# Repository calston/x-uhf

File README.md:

# X-UHF

The X-UHF is a modular RF prototyping system for amateur use.

This repo contains STL files and Kicad PCB designs and schematics for different modules.

## Testing

This table reflects modules which have actually been built and performance tested.

|Module      | PCB tested | Frequency tested | Design tested | 
|------------|------------|------------------|---------------|
|SA612 Module| Yes        | 50 Mhz           | Yes           |
|SI5351      | NO         | N/A              | NO            |
|SI5351-BX   | YES        | 100 Mhz          | Yes           |
|DRA818      | NO         | N/A              | NO            |

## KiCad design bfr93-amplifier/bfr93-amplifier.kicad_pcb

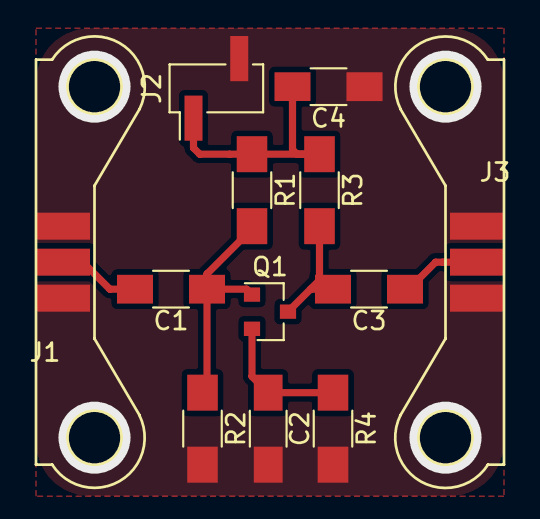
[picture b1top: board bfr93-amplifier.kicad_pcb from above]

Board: 2 copper layers, 12 parts (0 on the bottom side), 7 nets.

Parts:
C1, C2, C3: 100n; C_1206_HandSoldering
C4: 10u; C_1206_HandSoldering
J1: IN; X-UHF_Interconnect
J2: PWR; Pin_Header_Straight_1x02_Pitch2.54mm_SMD_Pin1Left
J3: OUT; X-UHF_Interconnect
Q1: BFR93A; SOT-23
R1, R2: 1K; R_1206_HandSoldering
R3, R4: 220; R_1206_HandSoldering

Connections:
Earth: C2.2, C4.1, J1.1, J1.3, J2.2, J3.1, J3.3, R2.2, R4.2
unnamed: C1.1, Q1.1, R1.2, R2.1
unnamed: C1.2, J1.2
unnamed: C2.1, Q1.2, R4.1
unnamed: C3.1, J3.2
unnamed: C3.2, Q1.3, R3.2
VCC: C4.2, J2.1, R1.1, R3.1

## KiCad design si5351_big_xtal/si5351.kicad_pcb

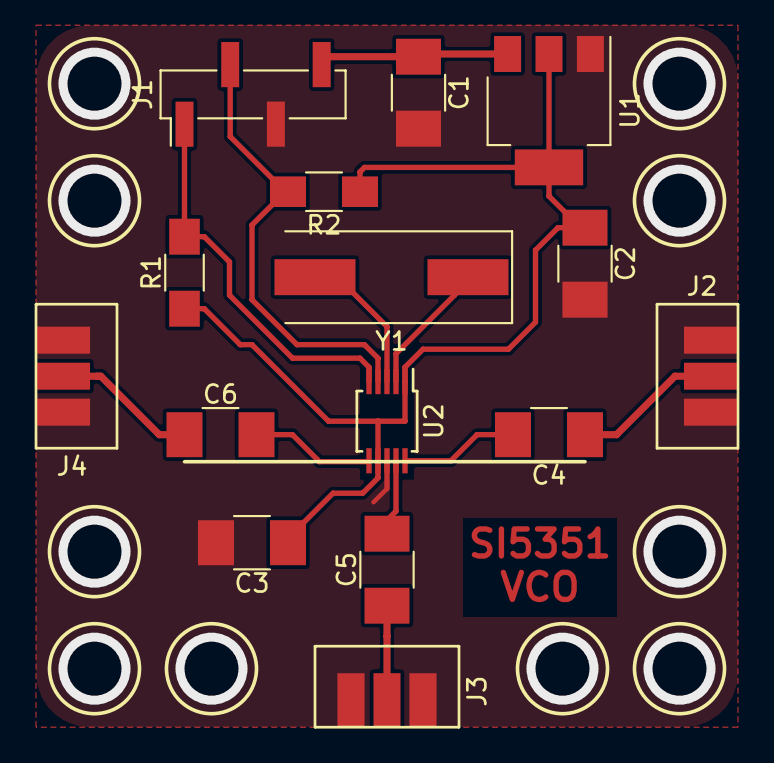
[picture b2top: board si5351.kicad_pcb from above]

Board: 2 copper layers, 15 parts (0 on the bottom side), 13 nets.

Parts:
C1: 10u; C_1210_HandSoldering
C2, C3: 1u; C_1210_HandSoldering
C4, C5, C6: 100n; C_1210_HandSoldering
J1: PWR_IIC; Pin_Header_Straight_1x04_Pitch2.54mm_SMD_Pin1Left
J2: CLK0; X-UHF_Interconnect
J3: CLK1; X-UHF_Interconnect
J4: CLK2; X-UHF_Interconnect
R1, R2: 10k; R_1206_HandSoldering
U1: LD1117-3.3; SOT-223-3_TabPin2
U2: SI5351A; MSOP-10_3x3mm_Pitch0.5mm
Y1: Crystal; Crystal_SMD_HC49-SD

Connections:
Earth: C1.2, C2.2, C3.2, J1.3, J2.1, J2.3, J3.1, J3.3, J4.1, J4.3, U1.1, U2.8
unnamed: C1.1, J1.4, U1.3
unnamed: C2.1, C3.1, R1.1, R2.1, U1.2, U2.1, U2.7
unnamed: C4.1, J2.2
unnamed: C4.2, U2.10
unnamed: C5.1, J3.2
unnamed: C5.2, U2.9
unnamed: C6.1, J4.2
unnamed: C6.2, U2.6
unnamed: J1.1, R1.2, U2.5
unnamed: J1.2, R2.2, U2.4
unnamed: U2.2, Y1.1
unnamed: U2.3, Y1.2

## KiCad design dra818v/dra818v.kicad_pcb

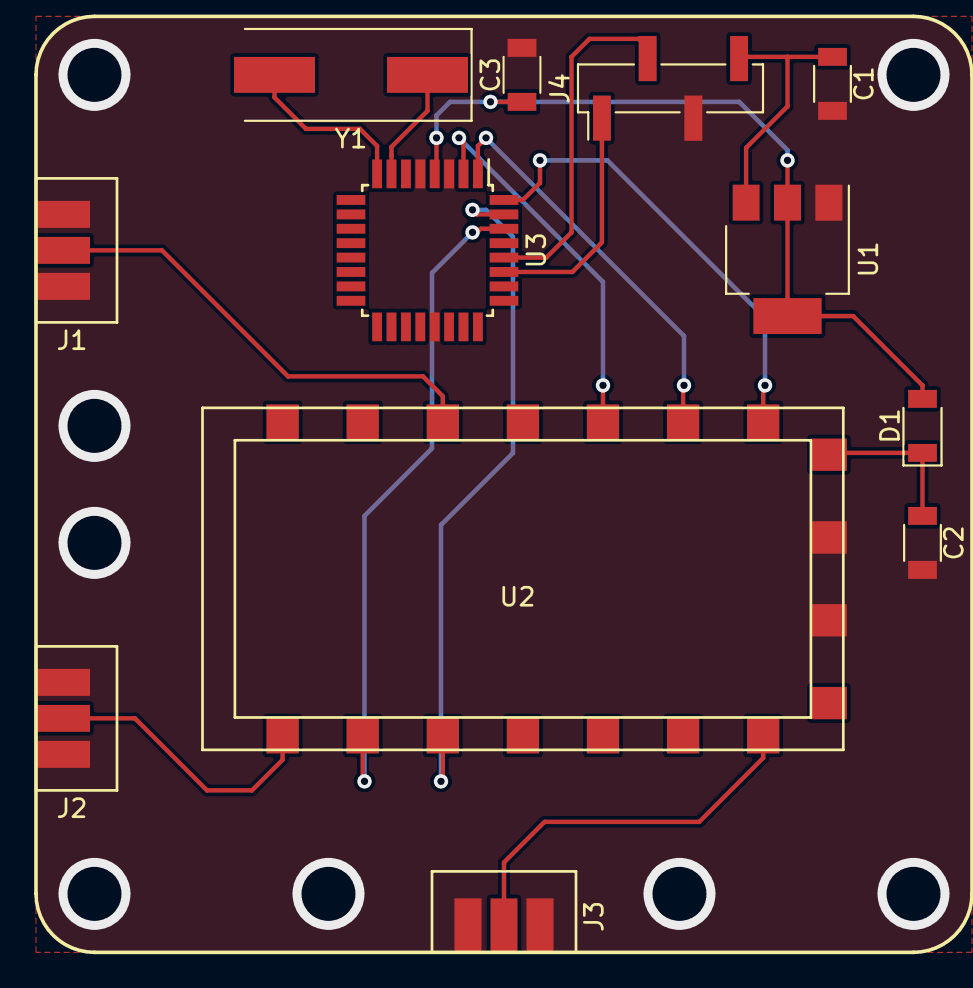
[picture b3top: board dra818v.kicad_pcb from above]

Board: 2 copper layers, 12 parts (0 on the bottom side), 16 nets.

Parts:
C1: 10uF; C_1206
C2, C3: 1uF; C_1206
D1: 1N4001; D_1206
J1: AF_OUT; X-UHF_Interconnect
J2: AF_IN; X-UHF_Interconnect
J3: RF; X-UHF_Interconnect
J4: Conn_01x04; Pin_Header_Straight_1x04_Pitch2.54mm_SMD_Pin1Left
U1: LD1117S50TR_SOT223; SOT-223-3_TabPin2
U2: DRA818V; DRA818
U3: ATmega328P-AU; TQFP-32_7x7mm_Pitch0.8mm
Y1: 16M; Crystal_SMD_HC49-SD

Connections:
Earth: C1.2, C2.2, C3.2, J1.1, J1.3, J2.1, J2.3, J3.1, J3.3, J4.3, U1.1, U2.9, U2.10, U3.3, U3.5, U3.21
unnamed: C1.1, J4.4, U1.3
unnamed: C2.1, D1.1, U2.8
unnamed: C3.1, D1.2, U1.2, U3.4, U3.6, U3.18
unnamed: J1.2, U2.3
unnamed: J2.2, U2.18
unnamed: J3.2, U2.12
unnamed: J4.1, U3.27
unnamed: J4.2, U3.28
unnamed: U2.5, U3.2
unnamed: U2.6, U3.1
unnamed: U2.7, U3.32
unnamed: U2.16, U3.31
unnamed: U2.17, U3.30
unnamed: U3.7, Y1.1
unnamed: U3.8, Y1.2

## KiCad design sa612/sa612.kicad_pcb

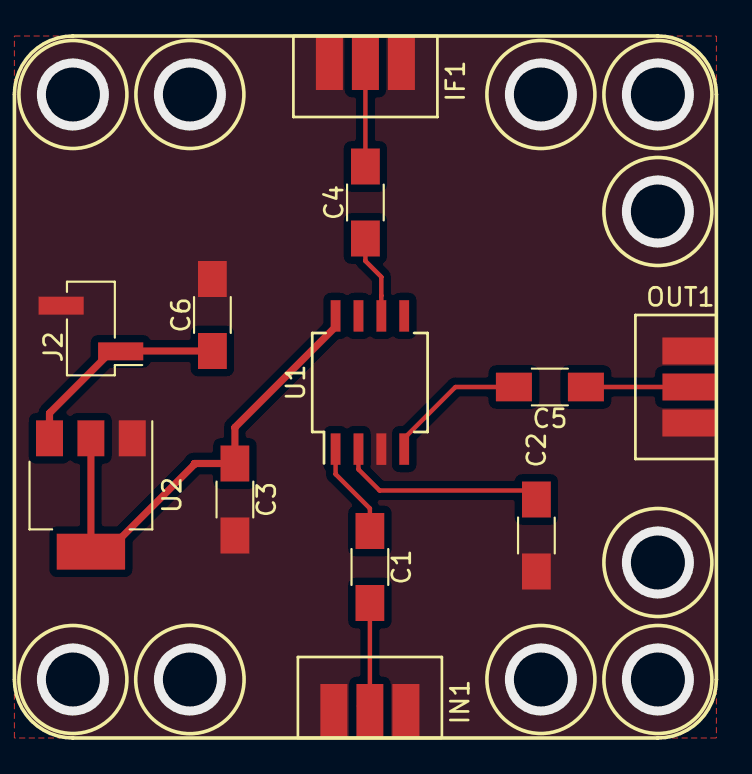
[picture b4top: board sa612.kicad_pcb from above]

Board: 2 copper layers, 12 parts (0 on the bottom side), 10 nets.

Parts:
C1, C2, C4: 10nF; C_1206_HandSoldering
C3: 1uF; C_1206_HandSoldering
C5, C6: 10uF; C_1206_HandSoldering
IF1: OSC_IN; X-UHF_Interconnect
IN1: RF_IN; X-UHF_Interconnect
J2: PWR; Pin_Header_Straight_1x02_Pitch2.54mm_SMD_Pin1Left
OUT1: RF_OUT; X-UHF_Interconnect
U1: SA612; SO-8_5.3x6.2mm_Pitch1.27mm
U2: LD1117S50TR_SOT223; SOT-223-3_TabPin2

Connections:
Earth: C2.1, C3.2, C6.2, IF1.1, IF1.3, IN1.1, IN1.3, J2.2, OUT1.1, OUT1.3, U1.3, U2.1
unnamed: C1.1, U1.1
unnamed: C1.2, IN1.2
unnamed: C2.2, U1.2
unnamed: C3.1, U1.8, U2.2
unnamed: C4.1, U1.6
unnamed: C4.2, IF1.2
unnamed: C5.1, OUT1.2
unnamed: C5.2, U1.4
unnamed: C6.1, J2.1, U2.3

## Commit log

2018-08-09 Initialise
2018-08-09 Clean up commit
2018-08-11 Fix the sa612 board layout
2018-08-11 Add DRA818 and SI5351 modules - untested!
2018-08-11 Add a warning
2018-08-17 Add DRA module
2018-08-17 Update the readme
2018-08-20 Si5351 design built tested as working!
2018-08-20 Move CLK0 and CLK2 capacitors to reduce distortion
2018-08-25 Add BFR93 amplifier module
2018-08-25 Update interconnect footprint to match GSG jumper
2018-08-26 Add power decoupling for amplifier
2018-09-06 FM demodulator and interface
